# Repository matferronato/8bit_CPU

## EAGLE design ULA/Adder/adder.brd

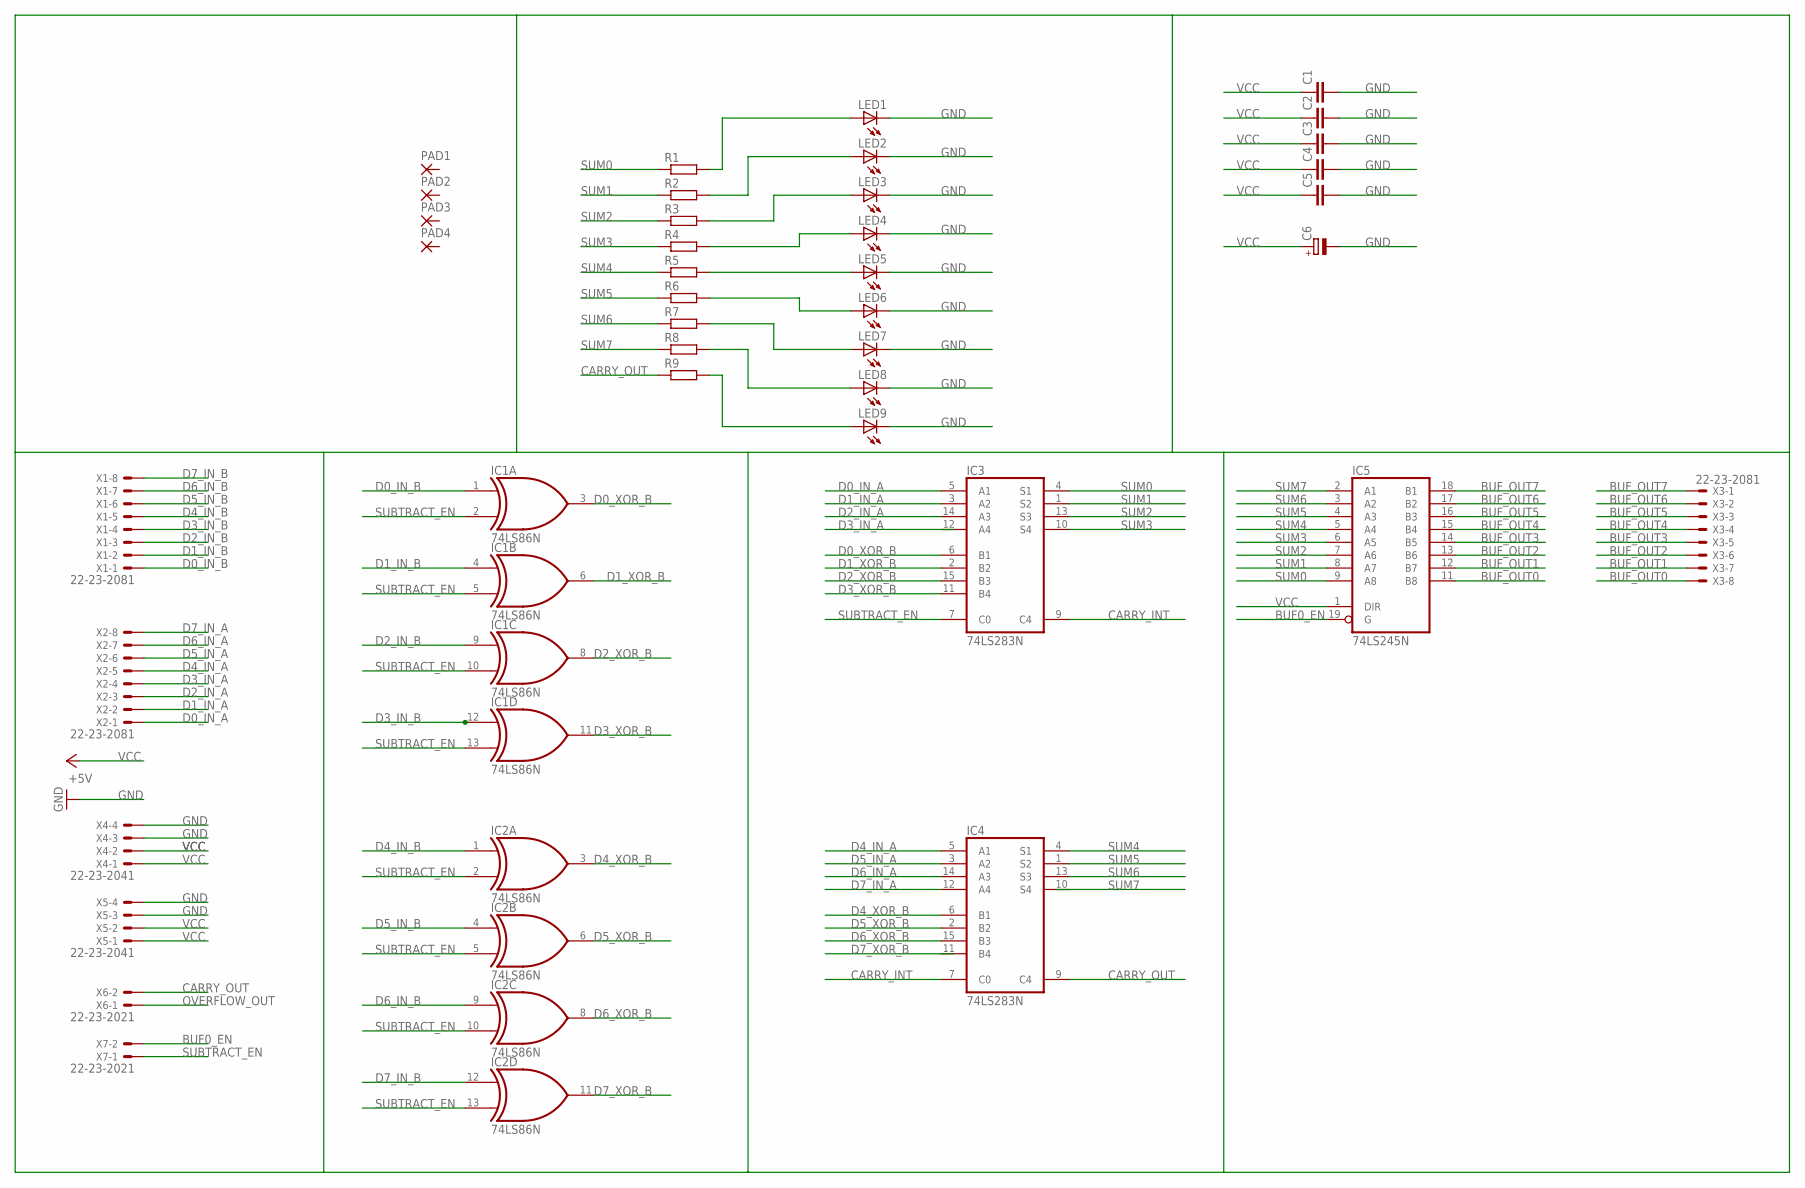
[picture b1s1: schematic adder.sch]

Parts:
C1, C2, C3, C4, C5: C-EU025-025X050; C025-025X050
C6: CPOL-EUE2.5-6; E2,5-6
IC1, IC2: 74LS86N; DIL14
IC3, IC4: 74LS283N; DIL16
IC5: 74LS245N; DIL20
LED1, LED2, LED3, LED4, LED5, LED6, LED7, LED8, LED9: LED5MM
PAD1, PAD2, PAD3, PAD4: 3,17/1,3
R1, R2, R3, R4, R5, R6, R7, R8, R9: R0207/10; 0207/10
X1, X2, X3: 22-23-2081
X4, X5: 22-23-2041
X6, X7: 22-23-2021

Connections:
BUF0_EN: IC5.19 (G), X7.2
BUF_OUT0: IC5.11 (B8), X3.8
BUF_OUT1: IC5.12 (B7), X3.7
BUF_OUT2: IC5.13 (B6), X3.6
BUF_OUT3: IC5.14 (B5), X3.5
BUF_OUT4: IC5.15 (B4), X3.4
BUF_OUT5: IC5.16 (B3), X3.3
BUF_OUT6: IC5.17 (B2), X3.2
BUF_OUT7: IC5.18 (B1), X3.1
CARRY_INT: IC3.9 (C4), IC4.7 (C0)
CARRY_OUT: IC4.9 (C4), R9.1, X6.2
D0_IN_A: IC3.5 (A1), X2.1
D0_IN_B: IC1.1 (I0), X1.1
D0_XOR_B: IC1.3 (O), IC3.6 (B1)
D1_IN_A: IC3.3 (A2), X2.2
D1_IN_B: IC1.4 (I0), X1.2
D1_XOR_B: IC1.6 (O), IC3.2 (B2)
D2_IN_A: IC3.14 (A3), X2.3
D2_IN_B: IC1.9 (I0), X1.3
D2_XOR_B: IC1.8 (O), IC3.15 (B3)
D3_IN_A: X2.4
D3_IN_B: IC1.12 (I0), X1.4
D3_XOR_B: IC1.11 (O), IC3.11 (B4)
D4_IN_A: IC4.5 (A1), X2.5
D4_IN_B: IC2.1 (I0), X1.5
D4_XOR_B: IC2.3 (O), IC4.6 (B1)
D5_IN_A: IC4.3 (A2), X2.6
D5_IN_B: IC2.4 (I0), X1.6
D5_XOR_B: IC2.6 (O), IC4.2 (B2)
D6_IN_A: IC4.14 (A3), X2.7
D6_IN_B: IC2.9 (I0), X1.7
D6_XOR_B: IC2.8 (O), IC4.15 (B3)
D7_IN_A: IC4.12 (A4), X2.8
D7_IN_B: IC2.12 (I0), X1.8
D7_XOR_B: IC2.11 (O)
GND: C1.2, C2.2, C3.2, C4.2, C5.2, C6.-, IC1.7 (GND), IC2.7 (GND), IC3.8 (GND), IC4.8 (GND), IC5.10 (GND), LED1.K (C), LED2.K (C), LED3.K (C), LED4.K (C), LED5.K (C), LED6.K (C), LED7.K (C), LED8.K (C), LED9.K (C), X4.3, X4.4, X5.3, X5.4
unnamed: LED1.A, R1.2
unnamed: LED2.A, R2.2
unnamed: LED3.A, R3.2
unnamed: LED4.A, R4.2
unnamed: LED5.A, R5.2
unnamed: LED9.A, R9.2
unnamed: LED8.A, R8.2
unnamed: LED7.A, R7.2
unnamed: LED6.A, R6.2
OVERFLOW_OUT: X6.1
SUBTRACT_EN: IC1.2 (I1), IC1.5 (I1), IC1.10 (I1), IC1.13 (I1), IC2.2 (I1), IC2.5 (I1), IC2.10 (I1), IC2.13 (I1), IC3.7 (C0), X7.1
SUM0: IC3.4 (S1), IC5.9 (A8), R1.1
SUM1: IC3.1 (S2), IC5.8 (A7), R2.1
SUM2: IC3.13 (S3), IC5.7 (A6), R3.1
SUM3: IC3.10 (S4), IC5.6 (A5), R4.1
SUM4: IC4.4 (S1), IC5.5 (A4), R5.1
SUM5: IC4.1 (S2), IC5.4 (A3), R6.1
SUM6: IC4.13 (S3), IC5.3 (A2), R7.1
SUM7: IC5.2 (A1), R8.1
VCC: C1.1, C2.1, C3.1, C4.1, C5.1, C6.+, IC1.14 (VCC), IC2.14 (VCC), IC3.16 (VCC), IC4.16 (VCC), IC5.1 (DIR), IC5.20 (VCC), X4.1, X4.2, X5.1, X5.2

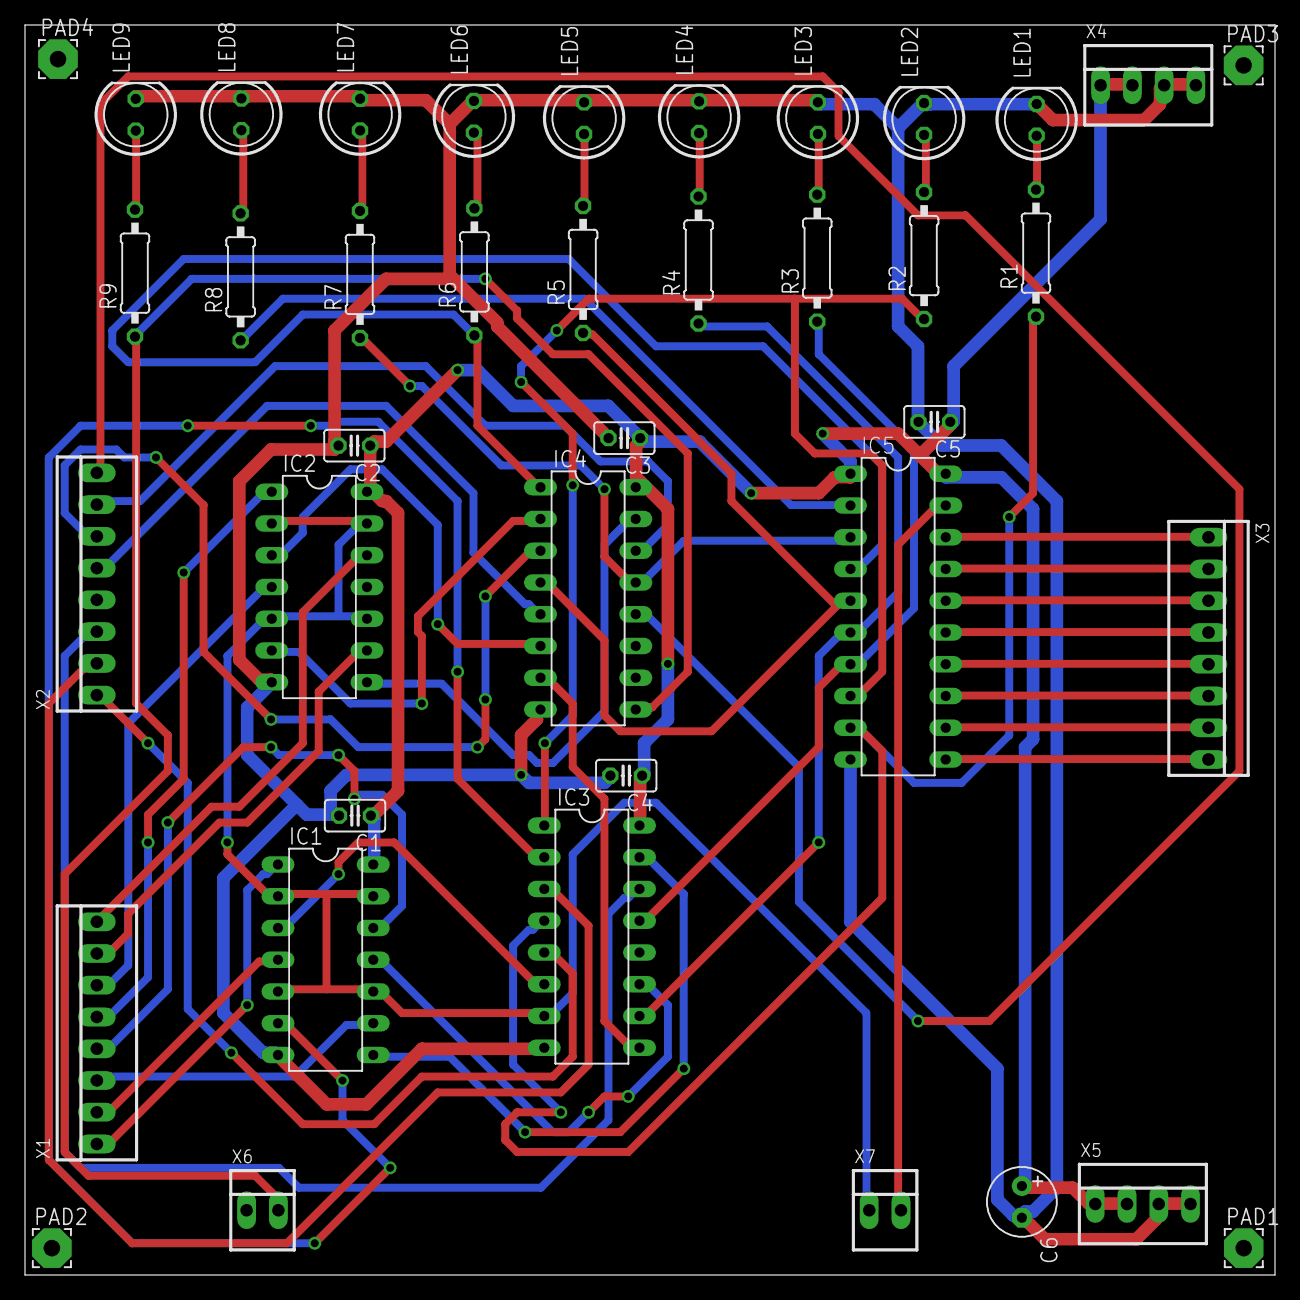
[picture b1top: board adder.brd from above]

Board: 2 copper layers, 100.0 x 100.0 mm, 40 parts (0 on the bottom side), 53 nets.

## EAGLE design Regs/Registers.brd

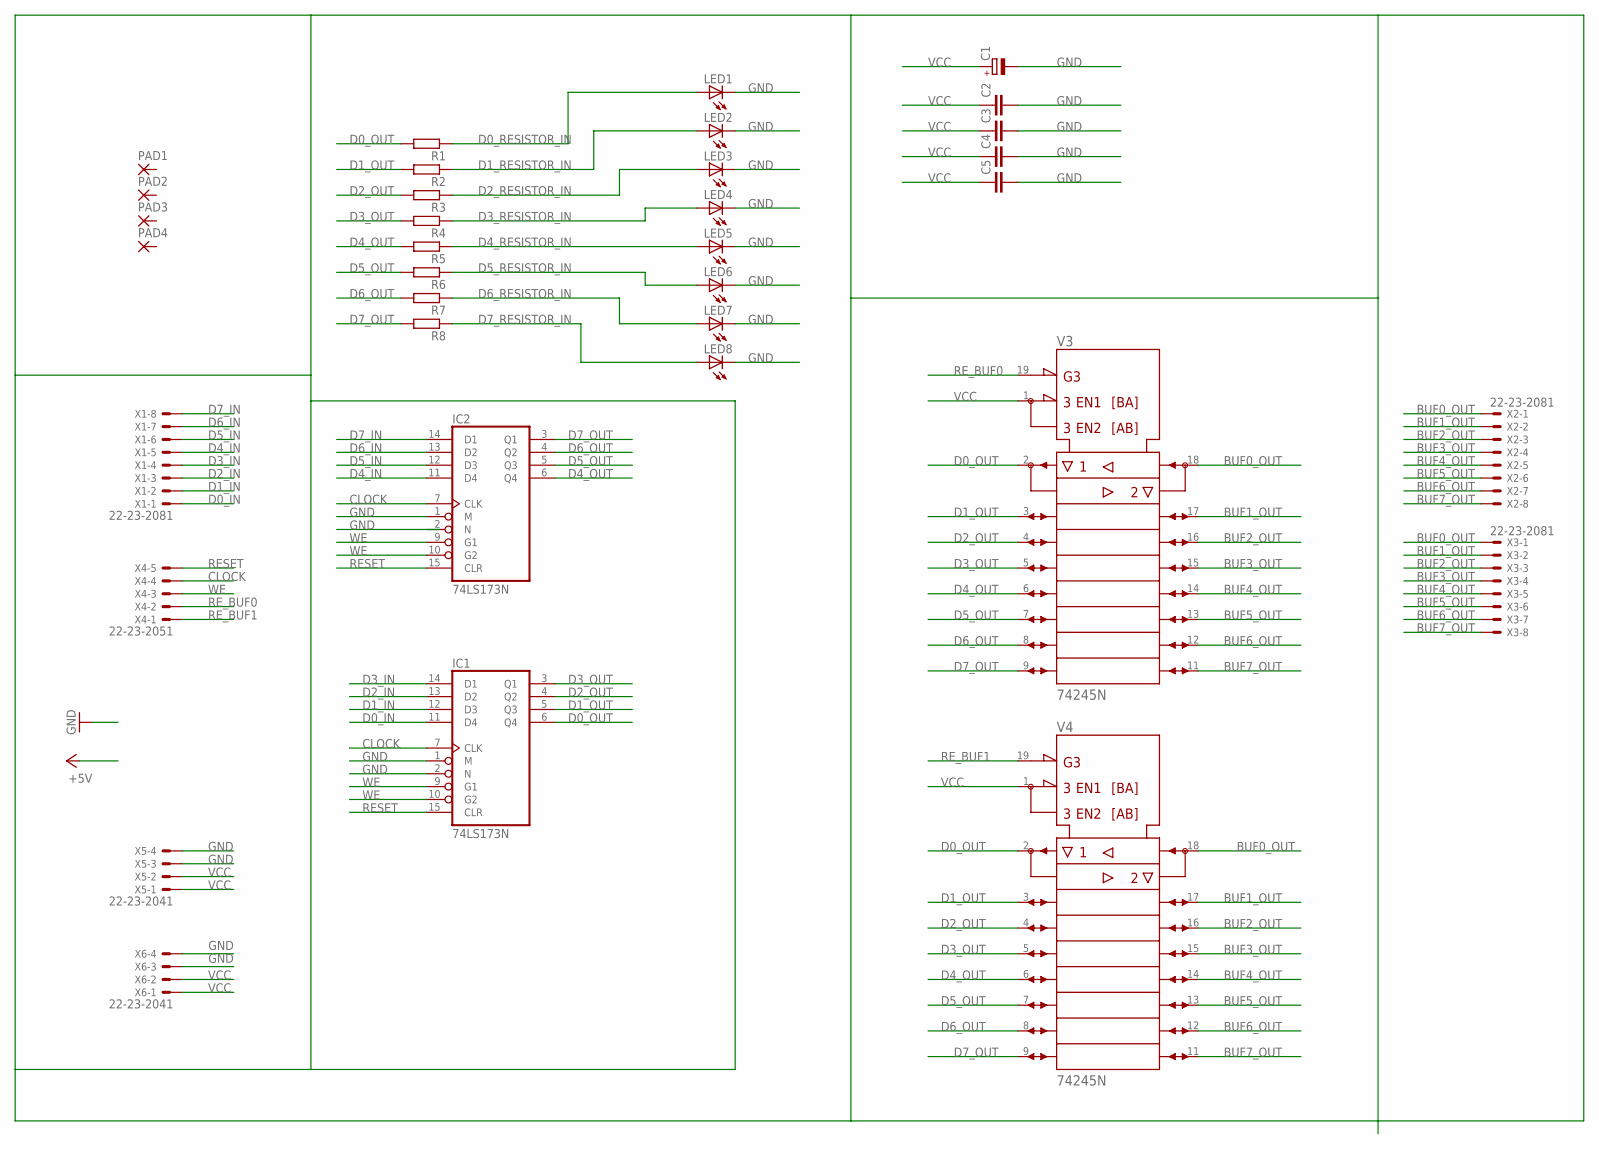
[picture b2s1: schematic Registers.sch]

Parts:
C1: CPOL-EUE2.5-6; E2,5-6
C2, C3, C4, C5: C-EU025-025X050; C025-025X050
IC1, IC2: 74LS173N; DIL16
LED1, LED2, LED3, LED4, LED5, LED6, LED7, LED8: LED5MM
PAD1, PAD2, PAD3, PAD4: 2,54/1,1
R1, R2, R3, R4, R5, R6, R7, R8: R0207/10; 0207/10
V3, V4: 74245N; DIL20
X1, X2, X3: 22-23-2081
X4: 22-23-2051
X5, X6: 22-23-2041

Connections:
BUF0_OUT: V3.18 (B1), V4.18 (B1), X2.1, X3.1
BUF1_OUT: V3.17 (B2), V4.17 (B2), X2.2, X3.2
BUF2_OUT: V3.16 (B3), V4.16 (B3), X2.3, X3.3
BUF3_OUT: V3.15 (B4), V4.15 (B4), X2.4, X3.4
BUF4_OUT: V3.14 (B5), V4.14 (B5), X2.5, X3.5
BUF5_OUT: V3.13 (B6), V4.13 (B6), X2.6, X3.6
BUF6_OUT: V3.12 (B7), V4.12 (B7), X2.7, X3.7
BUF7_OUT: V3.11 (B8), V4.11 (B8), X2.8, X3.8
CLOCK: IC1.7 (CLK), IC2.7 (CLK), X4.4
D0_IN: IC1.11 (D4), X1.1
D0_OUT: IC1.6 (Q4), R1.2, V3.2 (A1), V4.2 (A1)
D0_RESISTOR_IN: LED1.A, R1.1
D1_IN: IC1.12 (D3), X1.2
D1_OUT: IC1.5 (Q3), R2.2, V3.3 (A2), V4.3 (A2)
D1_RESISTOR_IN: LED2.A, R2.1
D2_IN: IC1.13 (D2), X1.3
D2_OUT: IC1.4 (Q2), R3.2, V3.4 (A3), V4.4 (A3)
D2_RESISTOR_IN: LED3.A, R3.1
D3_IN: IC1.14 (D1), X1.4
D3_OUT: IC1.3 (Q1), R4.2, V3.5 (A4), V4.5 (A4)
D3_RESISTOR_IN: LED4.A, R4.1
D4_IN: IC2.11 (D4), X1.5
D4_OUT: IC2.6 (Q4), R5.2, V3.6 (A5), V4.6 (A5)
D4_RESISTOR_IN: LED5.A, R5.1
D5_IN: IC2.12 (D3), X1.6
D5_OUT: IC2.5 (Q3), R6.2, V3.7 (A6), V4.7 (A6)
D5_RESISTOR_IN: LED6.A, R6.1
D6_IN: IC2.13 (D2), X1.7
D6_OUT: IC2.4 (Q2), R7.2, V3.8 (A7), V4.8 (A7)
D6_RESISTOR_IN: LED7.A, R7.1
D7_IN: IC2.14 (D1), X1.8
D7_OUT: IC2.3 (Q1), R8.2, V3.9 (A8), V4.9 (A8)
D7_RESISTOR_IN: LED8.A, R8.1
GND: C1.-, C2.2, C3.2, C4.2, C5.2, IC1.1 (M), IC1.2 (N), IC1.8 (GND), IC2.1 (M), IC2.8 (GND), LED1.K (C), LED2.K (C), LED3.K (C), LED4.K (C), LED5.K (C), LED6.K (C), LED7.K (C), LED8.K (C), V3.10 (-UB), V4.10 (-UB), X5.3, X5.4, X6.3, X6.4
RESET: IC1.15 (CLR), IC2.15 (CLR), X4.5
RE_BUF0: V3.19 (!G), X4.2
RE_BUF1: V4.19 (!G), X4.1
VCC: C1.+, C2.1, C3.1, C4.1, C5.1, IC1.16 (VCC), IC2.16 (VCC), V3.1 (DIR), V3.20 (+UB), V4.1 (DIR), V4.20 (+UB), X5.1, X5.2, X6.1, X6.2
WE: IC1.9 (G1), IC1.10 (G2), IC2.9 (G1), IC2.10 (G2), X4.3

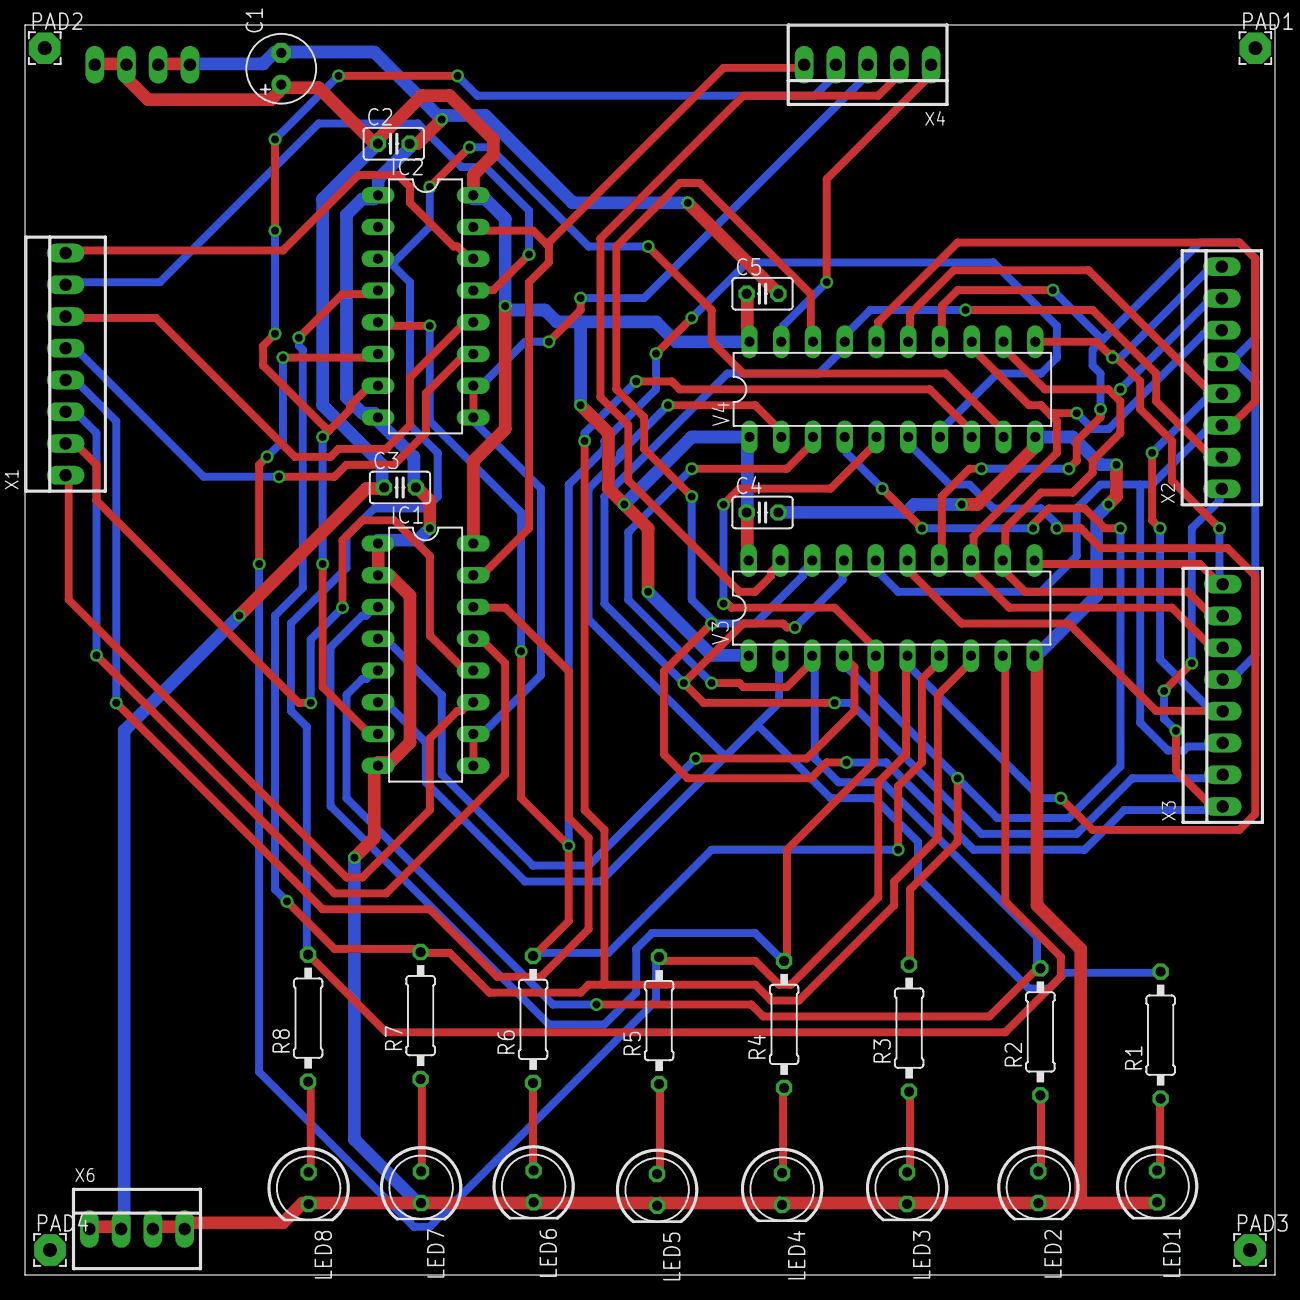
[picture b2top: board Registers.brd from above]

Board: 2 copper layers, 100.0 x 100.0 mm, 35 parts (1 on the bottom side), 39 nets.

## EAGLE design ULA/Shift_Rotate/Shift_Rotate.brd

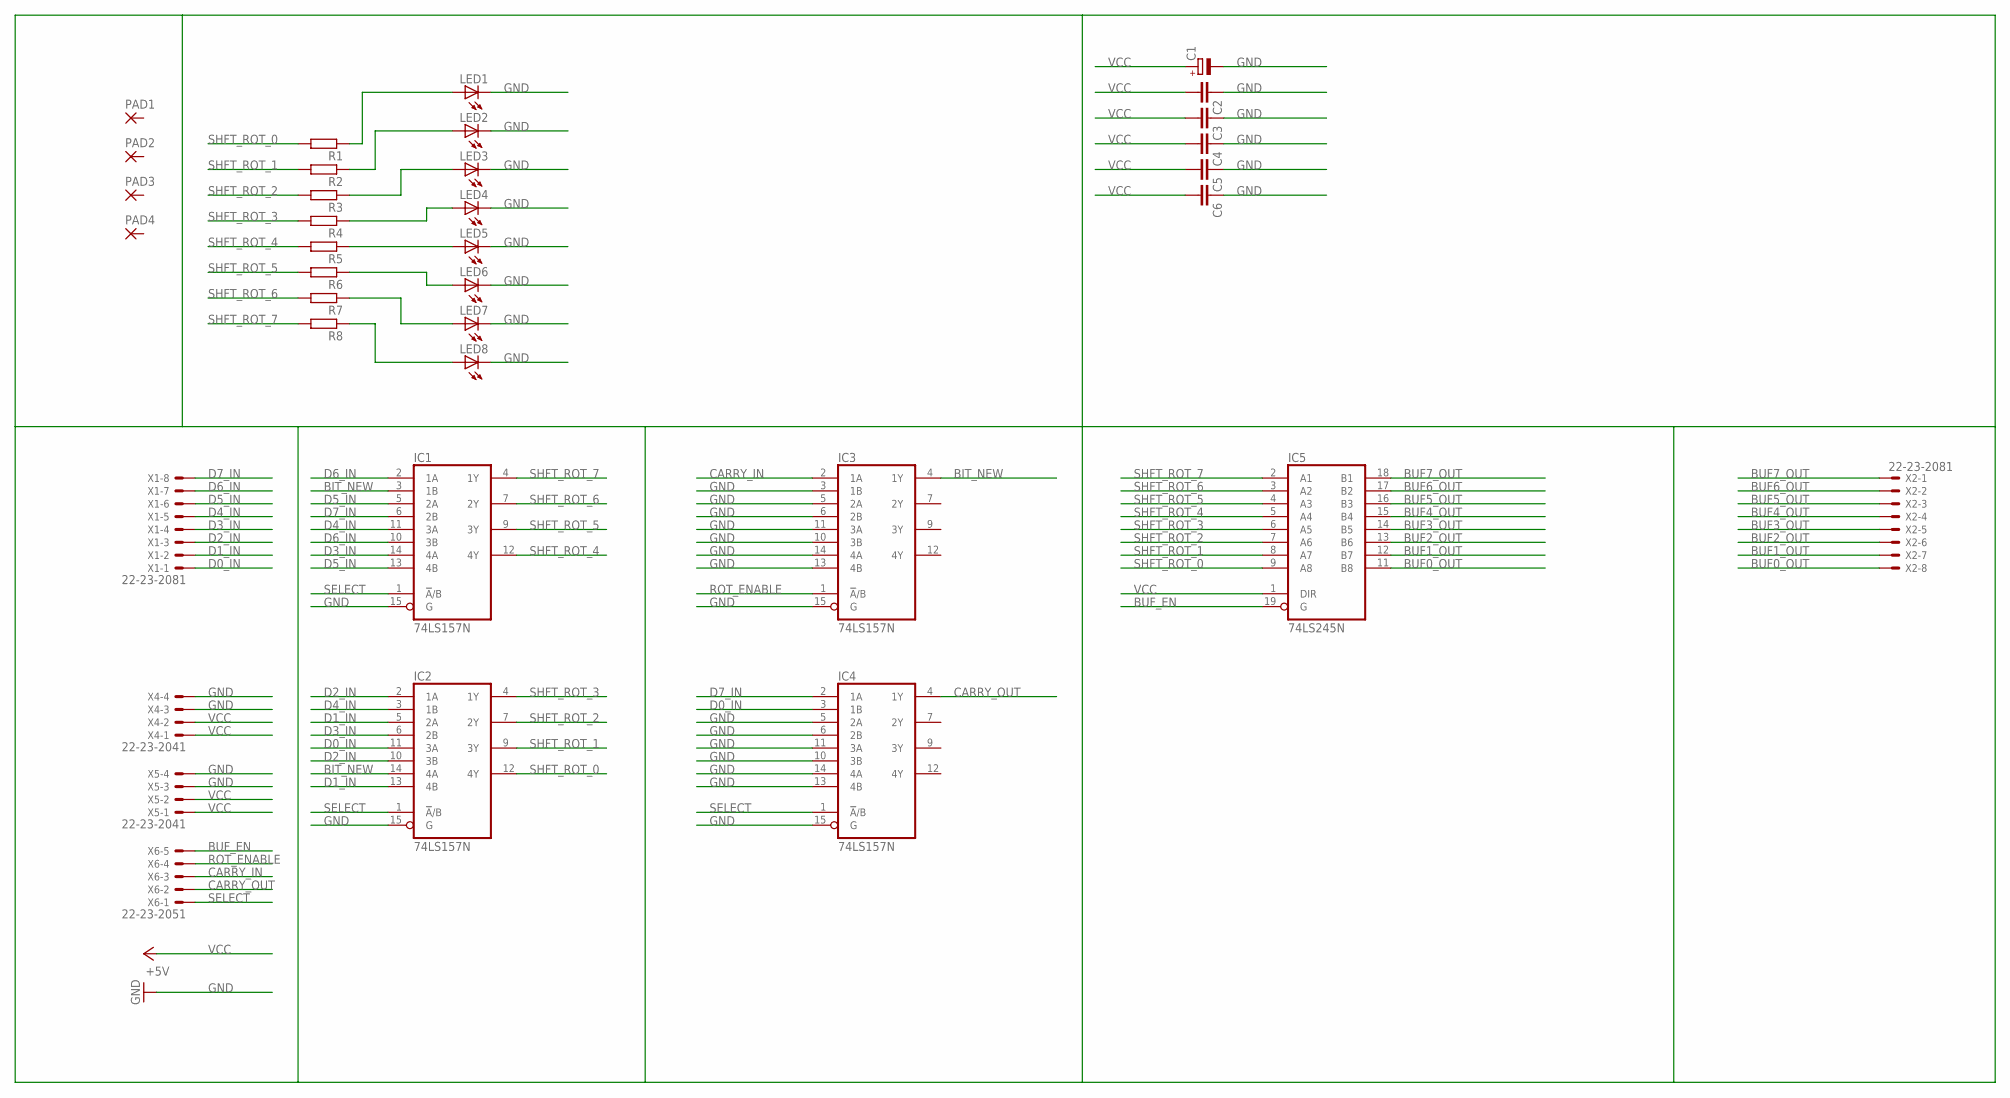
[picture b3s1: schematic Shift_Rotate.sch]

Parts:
C1: CPOL-EUE2.5-6; E2,5-6
C2, C3, C4, C5, C6: C-EU025-025X050; C025-025X050
IC1, IC2, IC3, IC4: 74LS157N; DIL16
IC5: 74LS245N; DIL20
LED1, LED2, LED3, LED4, LED5, LED6, LED7, LED8: LED5MM
PAD1, PAD2, PAD3, PAD4: 3,17/1,3
R1, R2, R3, R4, R5, R6, R7, R8: R0207/10; 0207/10
X1, X2: 22-23-2081
X4, X5: 22-23-2041
X6: 22-23-2051

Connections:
BIT_NEW: IC1.3 (1B), IC2.14 (4A), IC3.4 (1Y)
BUF0_OUT: IC5.11 (B8), X2.8
BUF1_OUT: IC5.12 (B7), X2.7
BUF2_OUT: IC5.13 (B6), X2.6
BUF3_OUT: IC5.14 (B5), X2.5
BUF4_OUT: IC5.15 (B4), X2.4
BUF5_OUT: IC5.16 (B3), X2.3
BUF6_OUT: IC5.17 (B2), X2.2
BUF7_OUT: IC5.18 (B1), X2.1
BUF_EN: IC5.19 (G), X6.5
CARRY_IN: IC3.2 (1A), X6.3
CARRY_OUT: IC4.4 (1Y), X6.2
D0_IN: IC2.11 (3A), IC4.3 (1B), X1.1
D1_IN: IC2.5 (2A), IC2.13 (4B), X1.2
D2_IN: IC2.2 (1A), IC2.10 (3B), X1.3
D3_IN: IC1.14 (4A), IC2.6 (2B), X1.4
D4_IN: IC1.11 (3A), IC2.3 (1B), X1.5
D5_IN: IC1.5 (2A), IC1.13 (4B), X1.6
D6_IN: IC1.2 (1A), IC1.10 (3B), X1.7
D7_IN: IC1.6 (2B), IC4.2 (1A), X1.8
GND: C1.-, C2.1, C3.1, C4.1, C5.1, C6.1, IC1.8 (GND), IC1.15 (G), IC2.8 (GND), IC2.15 (G), IC3.3 (1B), IC3.5 (2A), IC3.6 (2B), IC3.8 (GND), IC3.10 (3B), IC3.11 (3A), IC3.13 (4B), IC3.14 (4A), IC3.15 (G), IC4.5 (2A), IC4.6 (2B), IC4.8 (GND), IC4.10 (3B), IC4.11 (3A), IC4.13 (4B), IC4.14 (4A), IC4.15 (G), IC5.10 (GND), LED1.K (C), LED2.K (C), LED3.K (C), LED4.K (C), LED5.K (C), LED6.K (C), LED7.K (C), LED8.K (C), X4.3, X4.4, X5.3, X5.4
unnamed: LED1.A, R1.1
unnamed: LED2.A, R2.1
unnamed: LED3.A, R3.1
unnamed: LED4.A, R4.1
unnamed: LED5.A, R5.1
unnamed: LED6.A, R6.1
unnamed: LED7.A, R7.1
unnamed: LED8.A, R8.1
ROT_ENABLE: IC3.1 (!A!/B), X6.4
SELECT: IC1.1 (!A!/B), IC2.1 (!A!/B), IC4.1 (!A!/B), X6.1
SHFT_ROT_0: IC2.12 (4Y), IC5.9 (A8), R1.2
SHFT_ROT_1: IC2.9 (3Y), IC5.8 (A7), R2.2
SHFT_ROT_2: IC2.7 (2Y), IC5.7 (A6), R3.2
SHFT_ROT_3: IC2.4 (1Y), IC5.6 (A5), R4.2
SHFT_ROT_4: IC1.12 (4Y), IC5.5 (A4), R5.2
SHFT_ROT_5: IC1.9 (3Y), IC5.4 (A3), R6.2
SHFT_ROT_6: IC1.7 (2Y), IC5.3 (A2), R7.2
SHFT_ROT_7: IC1.4 (1Y), IC5.2 (A1), R8.2
VCC: C1.+, C2.2, C3.2, C4.2, C5.2, C6.2, IC1.16 (VCC), IC2.16 (VCC), IC3.16 (VCC), IC4.16 (VCC), IC5.1 (DIR), IC5.20 (VCC), X4.1, X4.2, X5.1, X5.2

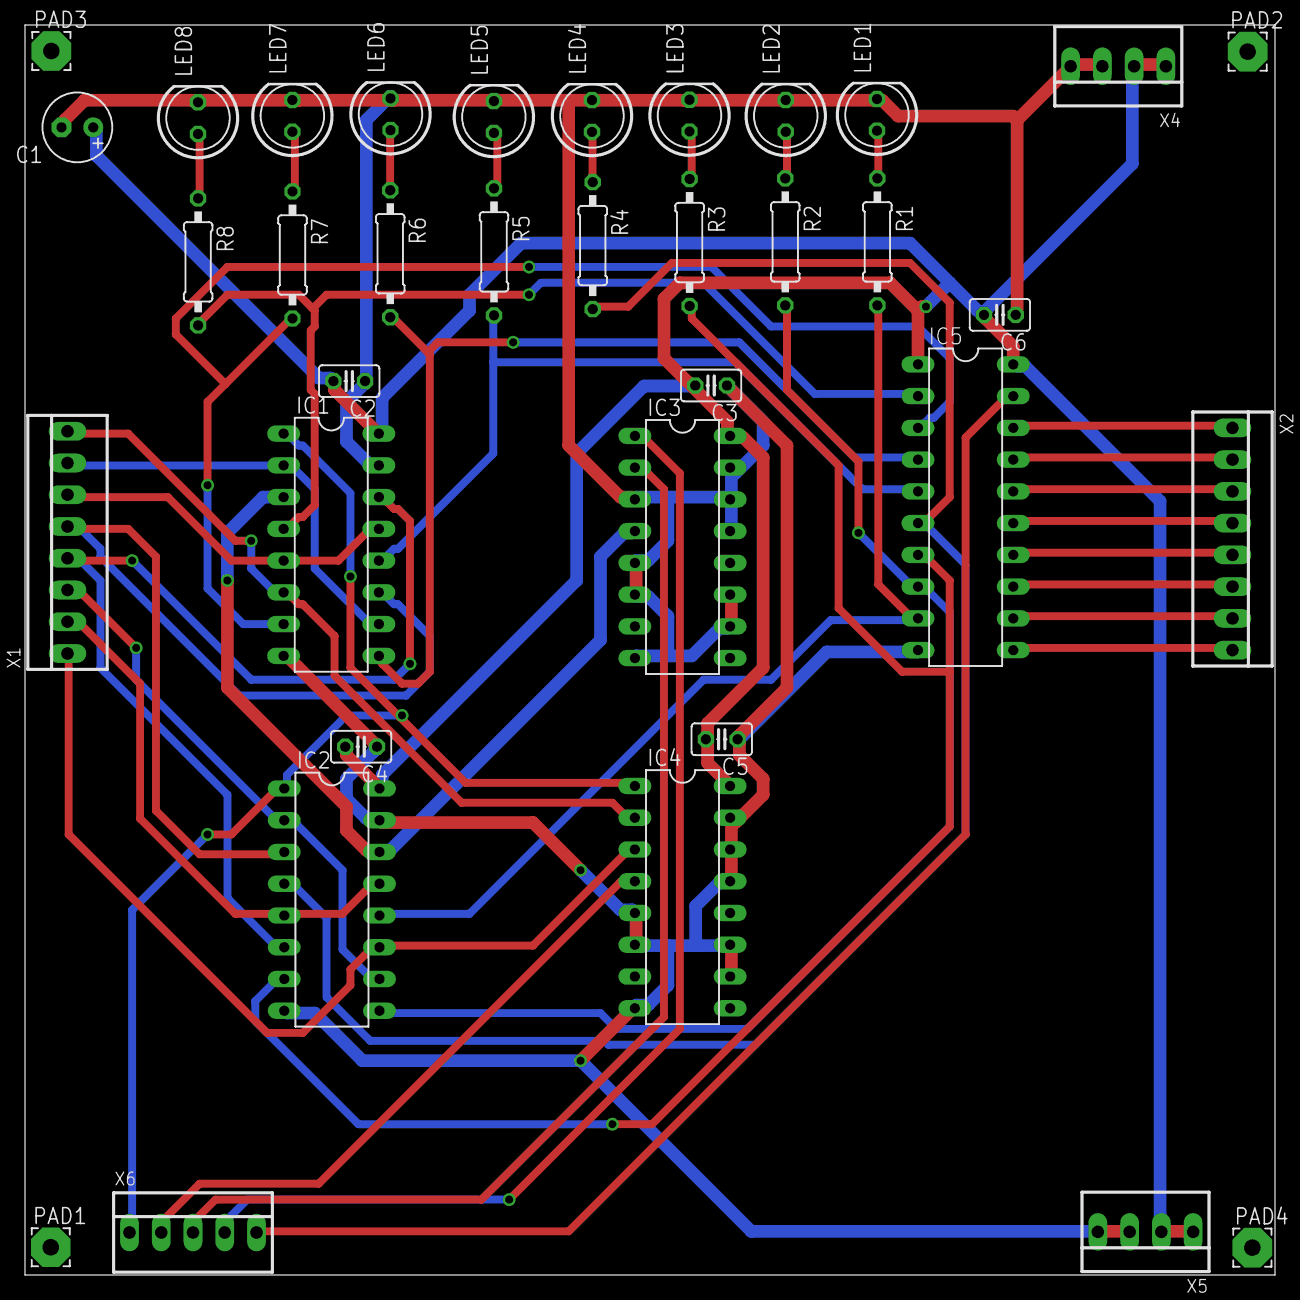
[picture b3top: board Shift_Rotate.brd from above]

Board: 2 copper layers, 100.0 x 100.0 mm, 36 parts (0 on the bottom side), 40 nets.

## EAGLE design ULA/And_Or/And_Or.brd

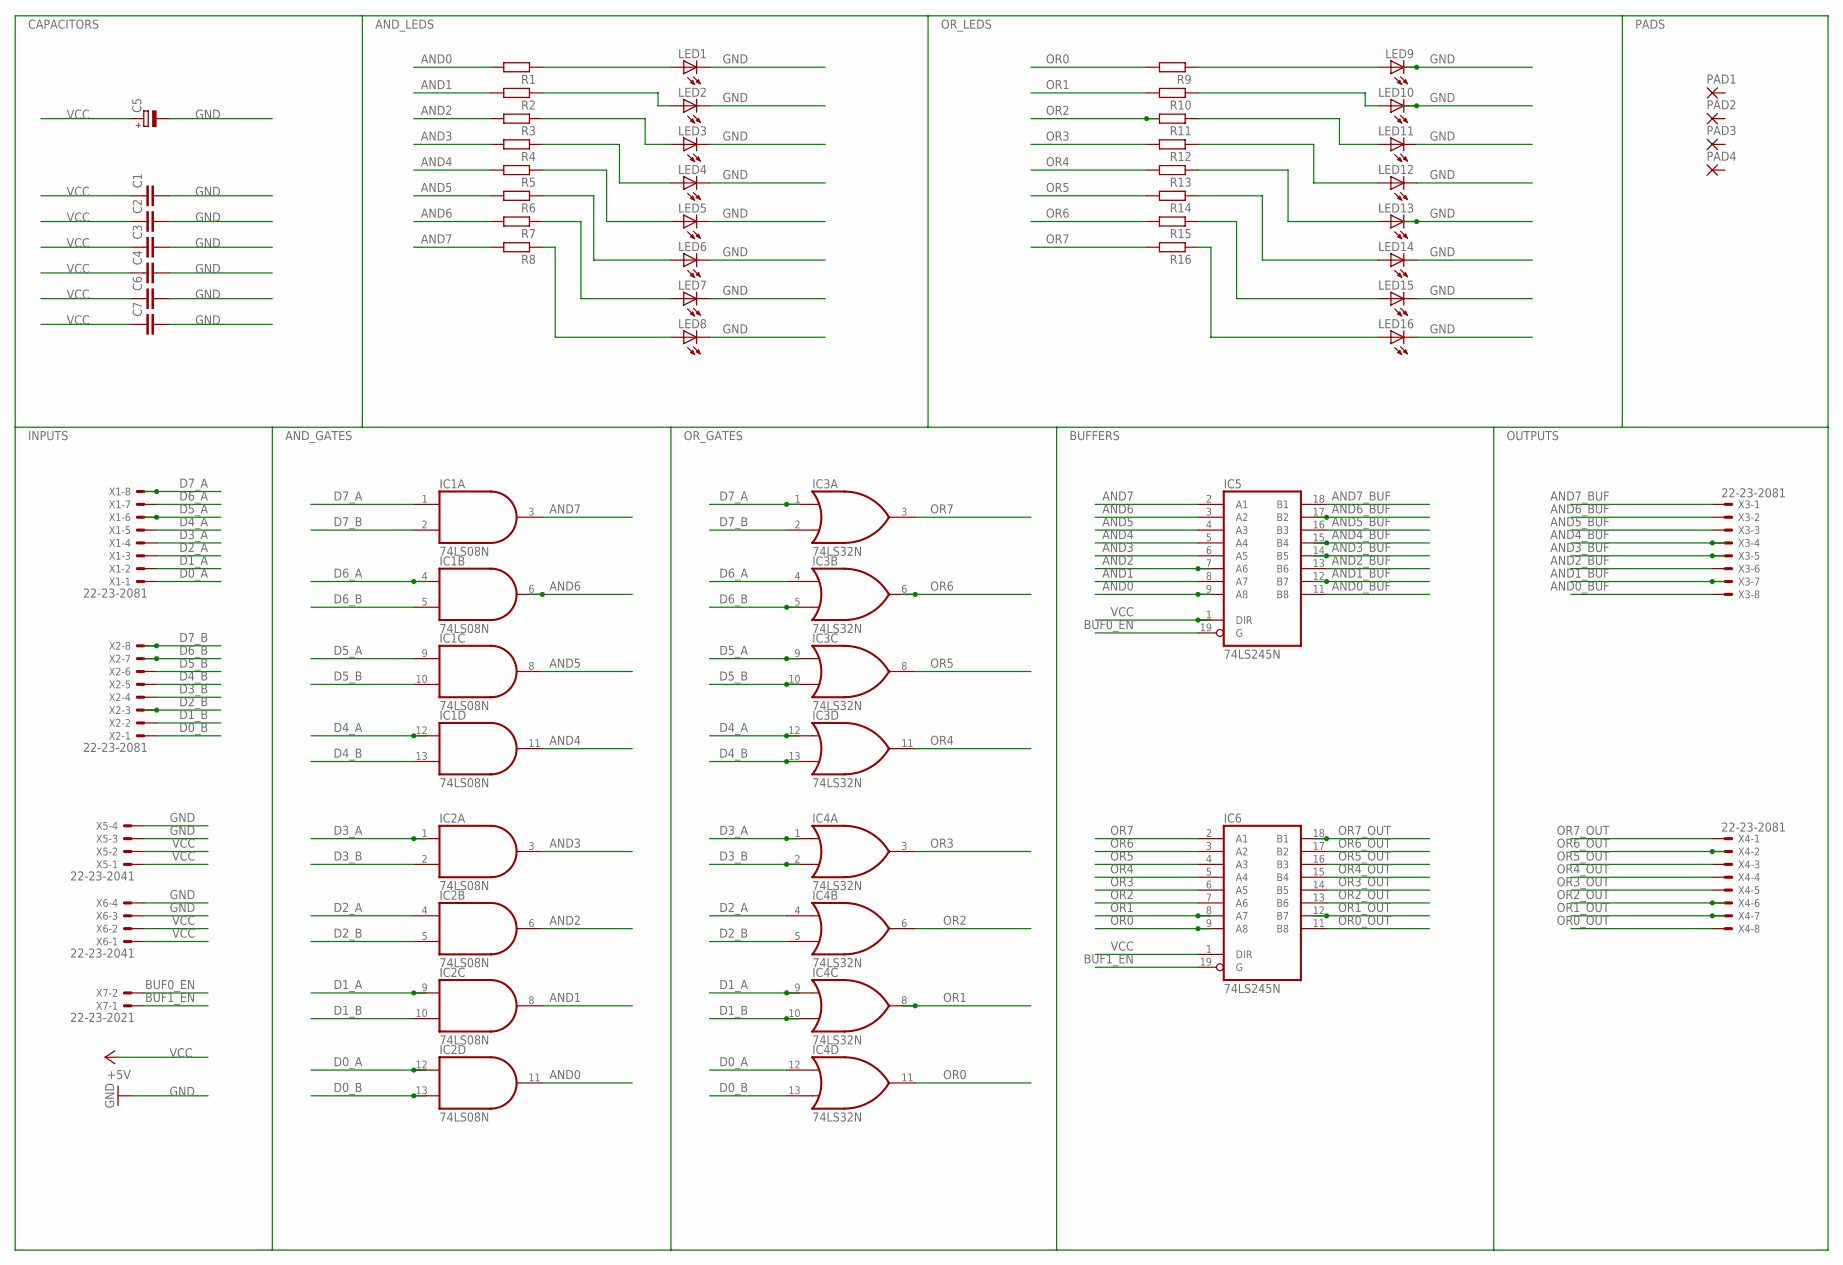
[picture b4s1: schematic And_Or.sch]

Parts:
C1, C2, C3, C4, C6, C7: C-EU025-025X050; C025-025X050
C5: CPOL-EUE2,5-6E; E2,5-6E
IC1, IC2: 74LS08N; DIL14
IC3, IC4: 74LS32N; DIL14
IC5, IC6: 74LS245N; DIL20
LED1, LED2, LED3, LED4, LED5, LED6, LED7, LED8, LED9, LED10, LED11, LED12, LED13, LED14, LED15, LED16: LED5MM
PAD1, PAD2, PAD3, PAD4: 3,17/1,3
R1, R2, R3, R4, R5, R6, R7, R8, R9, R10, R11, R12, R13, R14, R15, R16: R0207/10; 0207/10
X1, X2, X3, X4: 22-23-2081
X5, X6: 22-23-2041
X7: 22-23-2021

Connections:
AND0: IC2.11 (O), IC5.9 (A8), R1.2
AND0_BUF: IC5.11 (B8), X3.8
AND1: IC2.8 (O), IC5.8 (A7), R2.2
AND1_BUF: IC5.12 (B7), X3.7
AND2: IC2.6 (O), IC5.7 (A6), R3.2
AND2_BUF: IC5.13 (B6), X3.6
AND3: IC2.3 (O), IC5.6 (A5), R4.2
AND3_BUF: IC5.14 (B5), X3.5
AND4: IC1.11 (O), IC5.5 (A4), R5.2
AND4_BUF: IC5.15 (B4), X3.4
AND5: IC1.8 (O), IC5.4 (A3), R6.2
AND5_BUF: IC5.16 (B3), X3.3
AND6: IC1.6 (O), IC5.3 (A2), R7.2
AND6_BUF: IC5.17 (B2), X3.2
AND7: IC1.3 (O), IC5.2 (A1), R8.2
AND7_BUF: IC5.18 (B1), X3.1
BUF0_EN: IC5.19 (G), X7.2
BUF1_EN: IC6.19 (G), X7.1
D0_A: IC2.12 (I0), IC4.12 (I0), X1.1
D0_B: IC2.13 (I1), IC4.13 (I1), X2.1
D1_A: IC2.9 (I0), IC4.9 (I0), X1.2
D1_B: IC2.10 (I1), IC4.10 (I1), X2.2
D2_A: IC2.4 (I0), IC4.4 (I0), X1.3
D2_B: IC2.5 (I1), IC4.5 (I1), X2.3
D3_A: IC2.1 (I0), IC4.1 (I0), X1.4
D3_B: IC2.2 (I1), IC4.2 (I1), X2.4
D4_A: IC1.12 (I0), IC3.12 (I0), X1.5
D4_B: IC1.13 (I1), IC3.13 (I1), X2.5
D5_A: IC1.9 (I0), IC3.9 (I0), X1.6
D5_B: IC1.10 (I1), IC3.10 (I1), X2.6
D6_A: IC1.4 (I0), IC3.4 (I0), X1.7
D6_B: IC1.5 (I1), IC3.5 (I1), X2.7
D7_A: IC1.1 (I0), IC3.1 (I0), X1.8
D7_B: IC1.2 (I1), IC3.2 (I1), X2.8
GND: C1.2, C2.2, C3.2, C4.2, C5.-, C6.2, C7.2, IC1.7 (GND), IC2.7 (GND), IC3.7 (GND), IC4.7 (GND), IC5.10 (GND), IC6.10 (GND), LED1.K (C), LED2.K (C), LED3.K (C), LED4.K (C), LED5.K (C), LED6.K (C), LED7.K (C), LED8.K (C), LED9.K (C), LED10.K (C), LED11.K (C), LED12.K (C), LED13.K (C), LED14.K (C), LED15.K (C), LED16.K (C), X5.3, X5.4, X6.3, X6.4
unnamed: LED1.A, R1.1
unnamed: LED2.A, R2.1
unnamed: LED3.A, R3.1
unnamed: LED4.A, R4.1
unnamed: LED5.A, R5.1
unnamed: LED6.A, R6.1
unnamed: LED8.A, R8.1
unnamed: LED7.A, R7.1
unnamed: LED16.A, R16.1
unnamed: LED15.A, R15.1
unnamed: LED14.A, R14.1
unnamed: LED13.A, R13.1
unnamed: LED12.A, R12.1
unnamed: LED11.A, R11.1
unnamed: LED10.A, R10.1
unnamed: LED9.A, R9.1
OR0: IC4.11 (O), IC6.9 (A8), R9.2
OR0_OUT: IC6.11 (B8), X4.8
OR1: IC4.8 (O), IC6.8 (A7), R10.2
OR1_OUT: IC6.12 (B7), X4.7
OR2: IC4.6 (O), IC6.7 (A6), R11.2
OR2_OUT: IC6.13 (B6), X4.6
OR3: IC4.3 (O), IC6.6 (A5), R12.2
OR3_OUT: IC6.14 (B5), X4.5
OR4: IC3.11 (O), IC6.5 (A4), R13.2
OR4_OUT: IC6.15 (B4), X4.4
OR5: IC3.8 (O), IC6.4 (A3), R14.2
OR5_OUT: IC6.16 (B3), X4.3
OR6: IC3.6 (O), IC6.3 (A2), R15.2
OR6_OUT: IC6.17 (B2), X4.2
OR7: IC3.3 (O), IC6.2 (A1), R16.2
OR7_OUT: IC6.18 (B1), X4.1
VCC: C1.1, C2.1, C3.1, C4.1, C5.+, C6.1, C7.1, IC1.14 (VCC), IC2.14 (VCC), IC3.14 (VCC), IC4.14 (VCC), IC5.1 (DIR), IC5.20 (VCC), IC6.1 (DIR), IC6.20 (VCC), X5.1, X5.2, X6.1, X6.2

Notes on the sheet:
CAPACITORS
AND_LEDS
OR_LEDS
INPUTS
AND_GATES
OR_GATES
BUFFERS
OUTPUTS
PADS

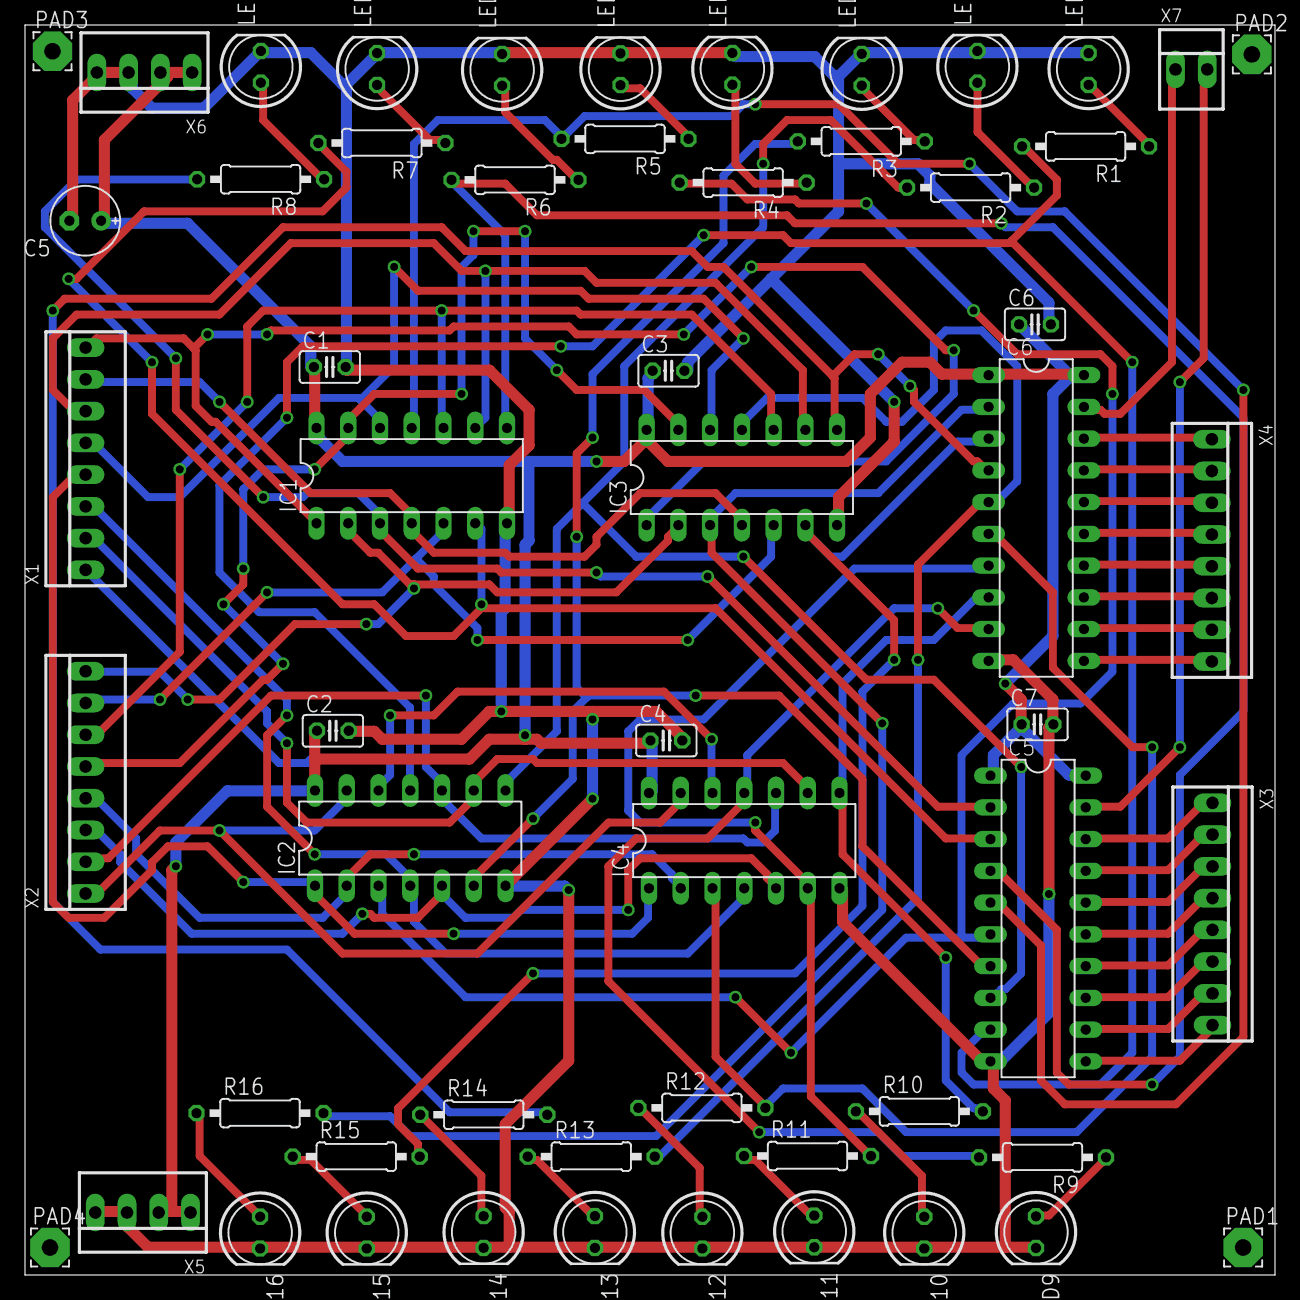
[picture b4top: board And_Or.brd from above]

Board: 2 copper layers, 100.0 x 100.0 mm, 56 parts (0 on the bottom side), 68 nets.
